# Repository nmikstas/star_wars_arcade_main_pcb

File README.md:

# star_wars_arcade_main_pcb
The source files for the reproduction of the 1983 Star Sars Arcade main PCB. The PCB is designed with Kicad. This project is complete and the PCB is verified working!

# Folder Structure
* BOM - Bill of materials for the main PCB
* Gerbers -The gerber files for the main PCB
* pcb - The Kicad design files for the main PCB

# PCB Specifications
* Layers: 2
* Dimensions: 293mm X 525mm
* Different PCB Design: 1
* PCB Thickness: 1.6mm
* Surface Finish: HASL
* Castellated Holes: No
* Copper Weight: 1oz.

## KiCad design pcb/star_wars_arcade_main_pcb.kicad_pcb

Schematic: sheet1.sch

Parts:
A_6, A_7: LS165A; DIP16
A_8: LS74; DIP14
A_9: LS164A; DIP14
B/C_0: LS138; DIP16
B_1: LS244B; DIP20
B_5: LS86; DIP14
B_6, B_7: LS165A; DIP16
B_8: LS385; DIP20
B_9: LS164A; DIP14
C1, C4, C5, C7, C8, C9, C10, C11, C12, C13, C14, C15, C16, C17, C18, C19, C20, C21, C22, C23, C24, C45, C46, C47, C48, C52, C53, C54, C55, C56, C57, C58, C59, C60, C61, C62, C63, C64, C65, C66, C67, C68, C69, C70, C71, C72, C73, C74, C75, C76, C77, C78, C79, C80, C81, C82, C83, C84, C85, C86, C87, C88, C89, C90, C91, C92, C95, C96: .1uf; GenericComp
C2: 100pf; CapBrown
C3: 39pf; CapBrown
C49, C50, C51: 100uf 35V; LargeCap
C93: 10uf 25V; Cap1
C94: 4.7uf; Cap1
CR1, CR3: 1N914; GenericComp
CR2: BLUE; LED
CR4, CR5, CR6: BLUE LED; LED
C_1: LS244C; DIP20
C_2: 68B09E; DDIP40
C_5: LS164A; DIP14
C_6, C_7: LS384; DIP16
C_8: LS08; DIP14
C_9, C_10: LS161; DIP16
D/E0: LS245A; DIP20
D_3: LS191_; DIP16
D_4, D_6, D_7: LS299; DIP20
D_5: LS164A; DIP14
D_8: LS00; DIP14
D_9: LS161; DIP16
E/F_2: LS244D; DIP20
E_1: x2212; DIP18
E_3: LS191_; DIP16
E_4: LS245A; DIP20
E_5, E_6: LS08; DIP14
E_7: LS00; DIP14
E_8: S02; DIP14
E_9: LS244; DIP20
F/H_2: 137211; DDIP24
F_1: 27128; DIP28
F_3: LS191_; DIP16
F_4: LS245A; DIP20
F_5: RAM; DDIP24
F_6: LS153A; DIP16
F_7: LS00; DIP14
F_8: S10; DIP14
F_9: LS244; DIP20
H/J_1: 2764; DIP28
H_3: LS157A; DIP16
H_4: LS245A; DIP20
H_5: RAM; DDIP24
H_6: LS191_; DIP16
H_7: PROM; DIP18
H_8: LS74; DIP14
H_9: LS244E; DIP20
J16: Aud_Conn; Aud_Con
J17: Main_Connector; J17
J18: Cat_Box_Conn; J21
J20: J20; Edge_Connector
J/K_1: 2764; DIP28
J_2: LS139; DIP16
J_3: LS153A; DIP16
J_4: LS244A; DIP20
J_5: LS164A; DIP14
J_6: LS191_; DIP16
J_7: PROM; DIP18
J_9: LS244F; DIP20
K/L_1: 2764; DIP28
K_2, K_6: LS08; DIP14
K_3: LS153A; DIP16
K_4: LS244A; DIP20
K_5: LS164A; DIP14
K_7: PROM; DIP18
K_8: LS04; DIP14
K_9: ADC; DIP28
L1: 100uH; Ind
L/M_9: LS259; DIP16
L_2, L_8: LS138; DIP16
L_3: LS157B; DIP16
L_4, L_5: LS374; DIP20
L_6: LS175D; DIP16
L_7: PROM; DIP18
L_10: 7407; DIP14
M_1: 2764; DIP28
M_2: LS74; DIP14
M_3: LS00; DIP14
M_4: LS374A; DIP20
M_5: LS374B; DIP20
M_6: LS83A; DIP16
M_7: LS299; DIP20
M_8: LS138; DIP16
N_1: S04; DIP14
N_2: LS161; DIP16
N_3: LS299; DIP20
N_4, N_5, N_6: LS83A; DIP16
N_7: LS138; DIP16
N_8: LS00; DIP14
N_11: 082; DIP8
P_2: LS393; DIP14
P_3: LS04; DIP14
P_4: LS175B; DIP16
P_5: LS175A; DIP16
P_6: LS175C; DIP16
P_7: LS74; DIP14
P_8: LS109; DIP16
Q1: 2N3904; GenericTrans
Q3, Q4: Q_NPN_BCE; VoltReg
R1, R2, R5, R11, R12, R15, R42, R43, R44, R45, R46, R47, R48, R49, R50, R51, R52, R53, R54, R55, R56, R57, R59: 10k; GenericComp
R3: 68; GenericComp
R4, R9, R10, R13, R14, R16, R17, R22, R23, R24, R25, R34, R35, R36, R37, R38, R39, R40, R41, R58, R91, R92, R93, R94, R95, R96, R97: 1k; GenericComp
R6: 100k; GenericComp
R7: 220; GenericComp
R8: 15k; GenericComp
R18, R19, R20, R21, R26, R27, R28, R29, R30, R31, R32, R33: 470; GenericComp
R79, R80, R81: 100; GenericComp
R82, R83, R84, R85, R86: 4.7k; GenericComp
R100: 22k; GenericComp
R1000: 180; GenericComp
R_2: LS393A; DIP14
R_3: LS161; DIP16
R_5: LS155; DIP16
R_6: LS74; DIP14
R_8: LS191_; DIP16
R_10: LS14; DIP14
SPARE1: SpareB; DIP16
SW1: L_11; DIP8
SW2: D_10; DIP16
SW3: E/F_10; DIP16
TP3MHZ1, TP6MHZ1: TP; TEST_POINT
TP+5V1, TP+5V2, TP+5V3, TP+5V4, TP+10.3UN1, TP+12V1: TP; TEST_POINT
TP-5V1: TP; TEST_POINT
TPCATSTR1: TP; TEST_POINT
TPCOINL1: TP; TEST_POINT
TPCOINR1: TP; TEST_POINT
TPCOIN_AUX1: TP; TEST_POINT
TPDIAGN1: TP; TEST_POINT
TPE1: TP; TEST_POINT
TPEVMEM1: TP; TEST_POINT
TPFIRE/START1: TP; TEST_POINT
TPGND1, TPGND2, TPGND3, TPGND4: TP; TEST_POINT
TPHALT1: TP; TEST_POINT
TPMPAGE1: TP; TEST_POINT
TPQ1: TP; TEST_POINT
TPRESET1: TP; TEST_POINT
TPROM0, TPROM1, TPROM2, TPROM3, TPROM4: TP; TEST_POINT
TPRST1, TPRST2: TP; TEST_POINT
TPRW1: TP; TEST_POINT
TPRWB1: TP; TEST_POINT
TPSELF_TEST1: TP; TEST_POINT
TPSLAM1: TP; TEST_POINT
TPWDDIS1: TP; TEST_POINT
VR1: L7805; VoltReg
Y1: 12.096MHz; Y

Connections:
1.5GCLK: D_9.12 (QC), F_7.13
1.5MHZ: B_1.11 (I0b), D_8.5, E_5.9, E_5.10, E_5.12, E_5.13, M_2.2 (1D), M_3.4, N_2.12 (QC), P_3.1
3GCLK: D_9.13 (QB), E_7.1
3MHZ: B_1.6 (I2a), C_5.8 (CLK), D_4.12 (CK~), D_5.8 (CLK), M_2.3 (1CLK), N_2.13 (QB), N_8.2, TP3MHZ1.1, TP3MHZ1.2
3MHZ*: M_3.13, M_4.11 (Cp), M_5.11 (Cp), M_7.3 (G2~), N_3.3 (G2~), P_8.10 (Q), R_6.11 (2CLK)
6MHZ: B_1.8 (I3a), N_2.14 (QA), P_3.11, TP6MHZ1.1, TP6MHZ1.2
12MHZ: C_9.2 (CLK), C_10.2 (CLK), D_9.2 (CLK), E_8.8, E_8.11, N_1.12, N_2.2 (CLK), R1000.1
750KHZ: K_9.10 (CLK), N_2.11 (QD), P_2.13 (2CK), R85.2
+5EAROM: C93.1, C95.2, CR3.1 (K), E_1.18 (VCC), R100.1, VR1.3 (OUT)
+5V: A_6.16 (VCC), A_7.16 (VCC), A_8.14 (VCC), A_9.14 (VCC), B/C_0.16 (VCC), B_1.20 (VCC), B_5.14 (VCC), B_6.16 (VCC), B_7.16 (VCC), B_8.20 (VCC), B_9.14 (VCC), C1.1, C5.1, C21.1, C22.1, C23.1, C24.1, C45.1, C49.1, C52.1, C53.1, C54.1, C55.1, C56.1, C57.1, C58.1, C59.1, C60.1, C61.1, C62.1, C63.1, C64.1, C65.1, C66.1, C67.1, C68.1, C69.1, C70.1, C71.1, C72.1, C73.1, C74.1, C75.1, C76.1, C77.1, C78.1, C79.1, C80.1, C81.1, C82.1, C83.1, C84.1, C85.1, C86.1, C87.1, C88.1, C89.1, C90.1, C91.1, C92.1, C96.1, CR1.1 (K), CR4.2 (A), CR5.2 (A), CR6.2 (A), C_1.20 (VCC), C_2.7 (VCC), C_5.14 (VCC), C_6.16 (VCC), C_7.16 (VCC), C_8.14 (VCC), C_9.16 (VCC), C_10.16 (VCC), D/E0.20 (VCC), D_3.16 (VCC), D_4.20 (VCC), D_5.14 (VCC), D_6.20 (VCC), D_7.20 (VCC), D_8.14 (VCC), D_9.16 (VCC), E/F_2.20 (VCC), E_3.16 (VCC), E_4.20 (VCC), E_5.14 (VCC), E_6.14 (VCC), E_7.14 (VCC), E_8.14 (VCC), E_9.20 (VCC), F/H_2.24 (VCC), F_1.1 (VPP), F_1.27 (PGM), F_1.28 (VCC), F_3.16 (VCC), F_4.20 (VCC), F_5.24 (VCC), F_6.16 (VCC), F_7.14 (VCC), F_8.14 (VCC), F_9.20 (VCC), H/J_1.1 (VPP), H/J_1.26 (NC), H/J_1.27 (PGM), H/J_1.28 (VCC), H_3.16 (VCC), H_4.20 (VCC), H_5.24 (VCC), H_6.16 (VCC), H_7.18 (VCC), H_8.14 (VCC), H_9.20 (VCC), J16.5 (+5V), J17.1 (5V0), J17.2 (5V0), J17.3 (5V0), J17.4 (5V0), J17.83 (5V0), J17.84 (5V0), J17.85 (5V0), J17.86 (5V0), J18.45 (5V0), J18.46 (5V0), J18.47 (5V0), J18.48 (5V0), J18.49 (5V0), J18.50 (5V0), J20.2 (+5V_REG), J20.21 (+SENSE), J20.B (+5V_REG), J20.Y (+5V_REG), J/K_1.1 (VPP), J/K_1.26 (NC), J/K_1.27 (PGM), J/K_1.28 (VCC), J_2.16 (VCC), J_3.16 (VCC), J_4.20 (VCC), J_5.14 (VCC), J_6.16 (VCC), J_7.18 (VCC), J_9.20 (VCC), K/L_1.1 (VPP), K/L_1.26 (NC), K/L_1.27 (PGM), K/L_1.28 (VCC), K_2.14 (VCC), K_3.16 (VCC), K_4.20 (VCC), K_5.14 (VCC), K_6.14 (VCC), K_7.18 (VCC), K_8.14 (VCC), K_9.11 (VCC), K_9.12 (REF+), L/M_9.16 (VCC), L_2.16 (VCC), L_3.16 (VCC), L_4.20 (VCC), L_5.20 (VCC), L_6.16 (VCC), L_7.18 (VCC), L_8.16 (VCC), L_10.14 (VCC), M_1.1 (VPP), M_1.26 (NC), M_1.27 (PGM), M_1.28 (VCC), M_2.14 (VCC), M_3.14 (VCC), M_4.20 (VCC), M_5.20 (VCC), M_6.5 (VCC), M_7.20 (VCC), M_8.16 (VCC), N_1.14 (VCC), N_2.16 (VCC), N_3.20 (VCC), N_4.5 (VCC), N_5.5 (VCC), N_6.5 (VCC), N_7.16 (VCC), N_8.14 (VCC), N_11.2 (-), P_2.14 (VCC), P_3.14 (VCC), P_4.16 (VCC), P_5.16 (VCC), P_6.16 (VCC), P_7.14 (VCC), P_8.16 (VCC), Q1.3 (C), R1.1, R4.1, R10.2, R11.2, R12.2, R15.2, R16.2, R17.2, R18.1, R19.1, R20.1, R21.1, R26.1, R27.1, R28.1, R29.1, R30.1, R31.1, R32.1, R33.1, R42.1, R43.1, R44.1, R45.1, R46.1, R47.1, R48.1, R49.1, R50.1, R51.1, R52.1, R53.1, R54.1, R55.1, R56.1, R57.1, R82.1, R83.1, R84.1, R85.1, R86.1, R91.1, R92.2, R93.2, R94.2, R95.2, R96.2, R97.1, R_2.14 (VCC), R_3.16 (VCC), R_5.16 (VCC), R_6.14 (VCC), R_8.16 (VCC), R_10.14 (VCC), SPARE1.16 (VCC), TP+5V1.1, TP+5V1.2, TP+5V2.1, TP+5V2.2, TP+5V3.1, TP+5V3.2, TP+5V4.1, TP+5V4.2
+10V: C4.1, J20.18 (+10_UNREG), J20.E (+10_UNREG), N_11.8 (VCC), R5.2, TP+10.3UN1.1, TP+10.3UN1.2
+12V: C51.1, J16.7 (+12V), J20.20 (+12VDC), J20.C (+12VDC), TP+12V1.1, TP+12V1.2, VR1.1 (IN)
-5V: C50.2, J16.6 (-5V), J20.19 (-5VDC), J20.D (-5VDC), TP-5V1.1, TP-5V1.2
A0: C_1.17 (I3b), C_2.8 (A0), J18.17 (A0)
A1: C_1.6 (I2a), C_2.9 (A1), J18.18 (A1)
A2: C_1.4 (I1a), C_2.10 (A2), J18.15 (A2)
A3: C_1.2 (I0a), C_2.11 (A3), J18.16 (A3)
A4: C_1.8 (I3a), C_2.12 (A4), J18.13 (A4)
A5: C_1.15 (I2b), C_2.13 (A5), J18.14 (A5)
A6: C_1.13 (I1b), C_2.14 (A6), J18.11 (A6)
A7: C_1.11 (I0b), C_2.15 (A7), J18.12 (A7)
A8: B_1.17 (I3b), C_2.16 (A8), J18.9 (A8)
A9: B_1.15 (I2b), C_2.17 (A9), J18.10 (A9)
A10: B_1.13 (I1b), C_2.18 (A10), J18.7 (A10)
A11: B_1.4 (I1a), C_2.19 (A11), J18.8 (A11)
A12: B_1.2 (I0a), C_2.20 (A12), J18.21 (A12)
A13: C_2.21 (A13), J18.22 (A13), K_2.9
A14: B/C_0.2 (B), C_2.22 (A14), J18.19 (A14)
A15: B/C_0.3 (C), C_2.23 (A15), J18.20 (A15), M_3.9
AB0: C_1.3 (O3b), E_1.6 (A0), F/H_2.8 (AB0), F_1.10 (A0), H/J_1.10 (A0), J17.43 (AB0), J17.44 (AB0), J/K_1.10 (A0), J_2.14 (2A), K/L_1.10 (A0), K_9.25 (ADDA), L/M_9.1 (A), M_1.10 (A0), N_7.1 (A), R83.2, R_5.3 (A1)
AB1: C_1.14 (O2a), E_1.5 (A1), F/H_2.7 (AB1), F_1.9 (A1), H/J_1.9 (A1), J17.35 (AB1), J17.36 (AB1), J/K_1.9 (A1), J_2.13 (2B), K/L_1.9 (A1), K_9.24 (ADDB), L/M_9.2 (B), L_3.14 (4A), M_1.9 (A1), N_7.2 (B), R82.2
AB2: C_1.16 (O1a), E_1.4 (A2), F/H_2.6 (AB2), F_1.8 (A2), H/J_1.8 (A2), J17.33 (AB2), J17.34 (AB2), J/K_1.8 (A2), K/L_1.8 (A2), L/M_9.3 (C), L_3.2 (1A), M_1.8 (A2), N_7.3 (C)
AB3: C_1.18 (O0a), E_1.3 (A3), F/H_2.5 (AB3), F_1.7 (A3), H/J_1.7 (A3), J17.31 (AB3), J17.32 (AB3), J/K_1.7 (A3), J_3.10 (2C0), K/L_1.7 (A3), M_1.7 (A3)
AB4: C_1.12 (O3a), E_1.2 (A4), F/H_2.4 (AB4), F_1.6 (A4), H/J_1.6 (A4), J17.45 (AB4), J17.46 (AB4), J/K_1.6 (A4), K/L_1.6 (A4), K_3.10 (2C0), M_1.6 (A4)
AB5: C_1.5 (O2b), E_1.16 (A5), F/H_2.3 (AB5), F_1.5 (A5), H/J_1.5 (A5), J17.37 (AB5), J17.38 (AB5), J/K_1.5 (A5), J_3.6 (1C0), K/L_1.5 (A5), L_8.1 (A), M_1.5 (A5), M_8.1 (A)
AB6: C_1.7 (O1b), E_1.17 (A6), F/H_2.2 (AB6), F_1.4 (A6), H/J_1.4 (A6), J17.41 (AB6), J17.42 (AB6), J/K_1.4 (A6), K/L_1.4 (A6), K_3.6 (1C0), L_8.2 (B), M_1.4 (A6), M_8.2 (B)
AB7: C_1.9 (O0b), E_1.1 (A7), F/H_2.1 (AB7), F_1.3 (A7), F_6.6 (1C0), H/J_1.3 (A7), J17.39 (AB7), J17.40 (AB7), J/K_1.3 (A7), K/L_1.3 (A7), L_8.3 (C), M_1.3 (A7), M_8.3 (C)
AB8: B_1.3 (O3b), F/H_2.23 (AB8), F_1.25 (A8), H/J_1.25 (A8), H_3.14 (4A), J17.47 (AB8), J17.48 (AB8), J/K_1.25 (A8), K/L_1.25 (A8), L_2.1 (A), M_1.25 (A8)
AB9: B_1.5 (O2b), F/H_2.22 (AB9), F_1.24 (A9), H/J_1.24 (A9), H_3.2 (1A), J17.49 (AB9), J17.50 (AB9), J/K_1.24 (A9), K/L_1.24 (A9), L_2.2 (B), M_1.24 (A9)
AB10: B_1.7 (O1b), F/H_2.19 (AB10), F_1.21 (A10), H/J_1.21 (A10), H_3.5 (2A), J17.51 (AB10), J17.52 (AB10), J/K_1.21 (A10), K/L_1.21 (A10), L_2.3 (C), M_1.21 (A10)
AB11: B_1.16 (O1a), F_1.23 (A11), H/J_1.23 (A11), H_3.11 (3A), J17.53 (AB11), J17.54 (AB11), J/K_1.23 (A11), J_2.2 (1A), K/L_1.23 (A11), M_1.23 (A11)
AB12: B_1.18 (O0a), F_1.2 (A12), H/J_1.2 (A12), J17.59 (AB12), J17.60 (AB12), J/K_1.2 (A12), J_2.3 (1B), K/L_1.2 (A12), M_1.2 (A12)
AB13: B/C_0.1 (A), J17.55 (AB13), J17.56 (AB13), K_2.8
BIC0: E_3.3 (QA), J_3.11 (2C1)
BIC1: E_3.2 (QB), K_3.11 (2C1)
BIC2: E_3.6 (QC), J_3.5 (1C1)
BIC3: E_3.7 (QD), K_3.5 (1C1)
BIC4: F_3.3 (QA), F_6.5 (1C1)
BIC5: F_3.2 (QB), H_3.13 (4B)
BIC6: F_3.6 (QC), H_3.3 (1B)
BIC7: F_3.7 (QD), H_3.6 (2B)
BIC8: D_3.3 (QA), H_3.10 (3B)
CIG*: K_5.2 (B), M_3.12, R_6.9 (2Q)
COIN_AUX: J20.P (COIN_AUX), R32.2, R39.2
COIN_CNTR_1: C7.1, J20.7 (COIN_CNTR_1), Q3.2 (C), SW1.1
COIN_CNTR_2: C8.1, J20.H (COIN_CNTR_2), Q4.2 (C), SW1.8
COIN_L: J20.N (COIN_L), R31.2, R40.2
COIN_R: J20.12 (COIN_R), R30.2, R41.2
D0: C_2.31 (D0), D/E0.11 (B7), E/F_2.18 (O0a), E_1.12 (IO1), E_4.11 (B7), E_9.3 (O3b), F/H_2.9 (D0), F_9.3 (O3b), H_9.7 (O1b), J18.29 (D0), J_9.3 (O3b), K_9.17 (D0)
D1: C_2.30 (D1), D/E0.12 (B6), E/F_2.16 (O1a), E_1.13 (IO2), E_4.12 (B6), E_9.5 (O2b), F/H_2.10 (D1), F_9.5 (O2b), H_9.16 (O1a), J18.30 (D1), J_9.5 (O2b), K_9.14 (D1)
D2: C_2.29 (D2), D/E0.13 (B5), E/F_2.12 (O3a), E_1.14 (IO3), E_4.13 (B5), E_9.7 (O1b), F/H_2.11 (D2), F_9.7 (O1b), H_9.18 (O0a), J18.27 (D2), J_9.7 (O1b), K_9.15 (D2)
D3: C_2.28 (D3), D/E0.14 (B4), E/F_2.3 (O3b), E_1.15 (IO4), E_4.14 (B4), E_9.9 (O0b), F/H_2.13 (D3), F_9.9 (O0b), H_9.3 (O3b), J18.28 (D3), J_9.16 (O1a), K_9.8 (D3)
D4: C_2.27 (D4), D/E0.15 (B3), E/F_2.5 (O2b), E_4.15 (B3), E_9.12 (O3a), F/H_2.14 (D4), F_9.12 (O3a), H_9.9 (O0b), J18.25 (D4), J_9.12 (O3a), K_9.18 (D4)
D5: C_2.26 (D5), D/E0.16 (B2), E/F_2.14 (O2a), E_4.16 (B2), E_9.14 (O2a), F/H_2.15 (D5), F_9.14 (O2a), H_9.12 (O3a), J18.26 (D5), J_9.14 (O2a), K_9.19 (D5)
D6: C_2.25 (D6), D/E0.17 (B1), E/F_2.7 (O1b), E_4.17 (B1), E_9.16 (O1a), F/H_2.16 (D6), F_9.16 (O1a), H_9.14 (O2a), J18.23 (D6), J_9.9 (O0b), K_9.20 (D6)
D7: C_2.24 (D7), D/E0.18 (B0), E/F_2.9 (O0b), E_4.18 (B0), E_9.18 (O0a), F/H_2.17 (D7), F_9.18 (O0a), H_9.5 (O2b), J18.24 (D7), J_9.18 (O0a), K_9.21 (D7), L/M_9.13 (D)
DB0: D_3.15 (A), D_4.16 (H~), E_3.15 (A), E_4.9 (A7), F_4.11 (B7), H_4.11 (B7), H_6.10 (C), J_4.12 (O3a), K_4.12 (O3a), L_4.13 (D4), L_5.18 (D7), L_6.13 (D3), P_4.5 (D1)
DB1: D_4.4 (G~), E_3.1 (B), E_4.8 (A6), F_4.12 (B6), H_4.12 (B6), H_6.9 (D), J_4.14 (O2a), K_4.14 (O2a), L_4.7 (D2), L_5.17 (D6), L_6.12 (D2), P_4.12 (D2)
DB2: D_4.15 (F~), E_3.10 (C), E_4.7 (A5), F_4.13 (B5), H_4.13 (B5), J_4.16 (O1a), J_6.15 (A), K_4.16 (O1a), L_4.14 (D5), L_5.14 (D5), P_4.13 (D3), P_6.13 (D3)
DB3: D_4.5 (E~), E_3.9 (D), E_4.6 (A4), F_4.14 (B4), H_4.14 (B4), J_4.18 (O0a), J_6.1 (B), K_4.18 (O0a), L_4.8 (D3), L_5.13 (D4), L_6.4 (D0), P_4.4 (D0)
DB4: D_4.14 (D~), E_4.5 (A3), F_3.15 (A), F_4.15 (B3), H_4.15 (B3), J_4.3 (O3b), J_6.10 (C), K_4.3 (O3b), L_4.18 (D7), L_5.8 (D3), L_6.5 (D1), P_5.12 (D2)
DB5: D_4.6 (C~), E_4.4 (A2), F_3.1 (B), F_4.16 (B2), H_4.16 (B2), J_4.5 (O2b), J_6.9 (D), K_4.5 (O2b), L_4.17 (D6), L_5.7 (D2), P_5.5 (D1), P_6.5 (D1)
DB6: D_4.13 (B~), E_4.3 (A1), F_3.10 (C), F_4.17 (B1), H_4.17 (B1), J_4.7 (O1b), K_4.7 (O1b), L_4.4 (D1), L_5.4 (D1), P_5.4 (D0), P_6.4 (D0), P_7.12 (2D)
DB7: D_4.7 (A~), E_4.2 (A0), F_3.9 (D), F_4.18 (B0), H_4.18 (B0), H_8.2 (1D), J_4.9 (O0b), K_4.9 (O0b), L_4.3 (D0), L_5.3 (D0), P_5.13 (D3), P_6.12 (D2)
DD0: L_5.19 (O7), M_5.19 (O7), M_6.11 (B1), M_7.16 (H~)
DD1: L_5.16 (O6), M_5.16 (O6), M_6.7 (B2), M_7.4 (G~)
DD2: L_5.15 (O5), M_5.15 (O5), M_6.4 (B3), M_7.15 (F~)
DD3: L_5.12 (O4), M_5.9 (O3), M_6.16 (B4), M_7.5 (E~)
DD4: L_5.9 (O3), M_5.12 (O4), M_7.14 (D~), N_6.11 (B1)
DD5: L_5.6 (O2), M_5.6 (O2), M_7.6 (C~), N_6.7 (B2)
DD6: L_5.5 (O1), M_5.5 (O1), M_7.13 (B~), N_6.4 (B3)
DD7: L_5.2 (O0), M_5.2 (O0), M_7.7 (A~), N_6.16 (B4)
DD8: L_4.12 (O4), M_4.9 (O3), N_3.16 (H~), N_4.11 (B1)
DD9: L_4.6 (O2), M_4.6 (O2), N_3.4 (G~), N_4.7 (B2)
DD10: L_4.15 (O5), M_4.15 (O5), N_3.15 (F~), N_4.4 (B3)
DD11: L_4.9 (O3), M_4.12 (O4), N_3.5 (E~), N_4.16 (B4)
DD12: L_4.19 (O7), M_4.2 (O0), N_3.14 (D~), N_5.11 (B1)
DD13: L_4.16 (O6), M_4.16 (O6), N_3.6 (C~), N_5.7 (B2)
DD14: L_4.5 (O1), M_4.5 (O1), N_3.13 (B~), N_5.4 (B3)
DD15: L_4.2 (O0), M_4.19 (O7), N_3.7 (A~), N_5.16 (B4)
DIAGN: J20.T (DIAGN), R18.2, R25.2
DS0: M_3.3, M_7.1 (S0~), N_3.1 (S0~)
DS1: M_7.19 (S1~), N_3.19 (S1~), N_8.8
E1.5MHZ: B_1.9 (O0b), J17.75 (1.5MHZ), J17.76 (1.5MHZ)
E3MHZ: B_1.14 (O2a), J17.69 (3MHZ), J17.70 (3MHZ)
E6MHZ: B_1.12 (O3a), J17.67 (6MHZ), J17.68 (6MHZ)
E12MHZ: J17.73 (12MHZ), J17.74 (12MHZ), N_1.10
ECLKQ: C_2.35 (Q), J17.77 (ECLKQ), J17.78 (ECLKQ), M_2.6 (~1Q), TPQ1.1, TPQ1.2
GND: A_6.8 (GND), A_6.15 (~CE), A_7.8 (GND), A_7.15 (~CE), A_8.7 (GND), A_9.7 (GND), B/C_0.4 (~G2A), B/C_0.5 (~G2B), B/C_0.8 (GND), B_1.1 (OEa), B_1.10 (GND), B_1.19 (OEb), B_5.7 (GND), B_6.8 (GND), B_6.15 (~CE), B_7.8 (GND), B_7.15 (~CE), B_8.8 (2S/~A), B_8.10 (GND), B_9.7 (GND), C1.2, C3.2, C4.2, C5.2, C7.2, C8.2, C9.2, C10.2, C11.2, C12.2, C13.2, C14.2, C15.2, C16.2, C17.2, C18.2, C19.2, C20.2, C21.2, C22.2, C23.2, C24.2, C45.2, C46.2, C47.2, C48.2, C49.2, C50.1, C51.2, C52.2, C53.2, C54.2, C55.2, C56.2, C57.2, C58.2, C59.2, C60.2, C61.2, C62.2, C63.2, C64.2, C65.2, C66.2, C67.2, C68.2, C69.2, C70.2, C71.2, C72.2, C73.2, C74.2, C75.2, C76.2, C77.2, C78.2, C79.2, C80.2, C81.2, C82.2, C83.2, C84.2, C85.2, C86.2, C87.2, C88.2, C89.2, C90.2, C91.2, C92.2, C93.2, C94.2, C95.1, C96.2, CR2.1 (K), C_1.1 (OEa), C_1.10 (GND), C_1.19 (OEb), C_2.1 (VSS), C_2.39 (TSC), C_5.7 (GND), C_6.8 (GND), C_6.9 (M), C_6.10 (K), C_7.8 (GND), C_8.7 (GND), C_9.4 (B), C_9.6 (D), C_9.8 (GND), C_10.8 (GND), D/E0.10 (GND), D_3.1 (B), D_3.4 (G), D_3.5 (D/U), D_3.8 (GND), D_3.9 (D), D_3.10 (C), D_4.10 (GND), D_4.19 (S1~), D_5.7 (GND), D_6.10 (GND), D_7.10 (GND), D_8.7 (GND), D_9.5 (C), D_9.8 (GND), E/F_2.10 (GND), E_1.8 (VSS), E_3.4 (G), E_3.5 (D/U), E_3.8 (GND), E_4.10 (GND), E_5.7 (GND), E_6.7 (GND), E_7.7 (GND), E_8.5, E_8.7 (GND), E_8.12, E_9.10 (GND), F/H_2.12 (GND), F_1.14 (GND), F_1.22 (~OE), F_3.4 (G), F_3.5 (D/U), F_3.8 (GND), F_4.10 (GND), F_5.12 (GND), F_5.18 (~CE), F_5.20 (~OE), F_6.1 (~1G), F_6.8 (GND), F_6.15 (~2G), F_7.7 (GND), F_8.7 (GND), F_9.10 (GND), H/J_1.14 (GND), H/J_1.22 (~OE), H_3.8 (GND), H_4.10 (GND), H_5.12 (GND), H_5.18 (~CE), H_5.20 (~OE), H_6.1 (B), H_6.4 (G), H_6.5 (D/U), H_6.8 (GND), H_6.15 (A), H_7.8 (~CE1), H_7.9 (GND), H_7.10 (~CE2), H_8.7 (GND), H_8.12 (2D), H_9.10 (GND), J16.4 (AUD_GND), J17.5 (GND), J17.6 (GND), J17.7 (GND), J17.8 (GND), J17.9 (GND), J17.10 (GND), J17.79 (GND), J17.80 (GND), J17.81 (GND), J17.82 (GND), J18.1 (GND), J18.2 (GND), J18.3 (GND), J18.4 (GND), J18.6 (GND), J18.34 (NC), J20.1 (+5V_RTN), J20.3 (GND), J20.4 (GND), J20.13 (GND), J20.22 (-SENSE), J20.A (+5V_RTN), J20.F (GND), J20.R (GND), J20.Z (+5V_RTN), J/K_1.14 (GND), J/K_1.22 (~OE), J_2.8 (GND), J_3.1 (~1G), J_3.8 (GND), J_3.15 (~2G), J_4.10 (GND), J_5.7 (GND), J_6.4 (G), J_6.5 (D/U), J_6.8 (GND), J_7.8 (~CE1), J_7.9 (GND), J_7.10 (~CE2), J_9.10 (GND), K/L_1.14 (GND), K/L_1.22 (~OE), K_2.7 (GND), K_3.1 (~1G), K_3.8 (GND), K_3.15 (~2G), K_4.10 (GND), K_5.7 (GND), K_6.7 (GND), K_7.8 (~CE1), K_7.9 (GND), K_7.10 (~CE2), K_8.7 (GND), K_9.1 (IN3), K_9.2 (IN4), K_9.3 (IN5), K_9.4 (IN6), K_9.5 (IN7), K_9.13 (GND), K_9.16 (GND), K_9.23 (ADDC), L/M_9.8 (GND), L_2.8 (GND), L_3.8 (GND), L_3.15 (E), L_4.10 (GND), L_5.10 (GND), L_6.8 (GND), L_7.8 (~CE1), L_7.9 (GND), L_7.10 (~CE2), L_8.8 (GND), L_10.7 (GND), M_1.14 (GND), M_1.22 (~OE), M_2.7 (GND), M_3.7 (GND), M_4.10 (GND), M_5.10 (GND), M_5.18 (D7), M_6.12 (GND), M_7.10 (GND), M_7.18 (SL), M_8.8 (GND), N_1.7 (GND), N_2.8 (GND), N_3.10 (GND), N_4.12 (GND), N_5.12 (GND), N_6.12 (GND), N_7.8 (GND), N_8.7 (GND), N_11.4 (VSS), P_2.7 (GND), P_3.7 (GND), P_4.8 (GND), P_5.8 (GND), P_6.8 (GND), P_7.2 (1D), P_7.7 (GND), P_8.2 (J), P_8.3 (K), P_8.8 (GND), P_8.13 (K), Q3.3 (E), Q4.3 (E), R2.2, R3.1, R7.1, R8.2, R1000.2, R_2.7 (GND), R_3.3 (A), R_3.4 (B), R_3.6 (D), R_3.8 (GND), R_5.8 (GND), R_6.7 (GND), R_8.1 (B), R_8.5 (D/U), R_8.8 (GND), R_8.9 (D), R_8.10 (C), R_10.7 (GND), SPARE1.8 (GND), SW2.9, SW2.10, SW2.11, SW2.12, SW2.13, SW2.14, SW2.15, SW2.16, SW3.9, SW3.10, SW3.11, SW3.12, SW3.13, SW3.14, SW3.15, SW3.16, TPGND1.1, TPGND1.2, TPGND2.1, TPGND2.2, TPGND3.1, TPGND3.2, TPGND4.1, TPGND4.2, TPRST1.1, TPRST1.2, VR1.2 (GND), Y1.2
IP0: L_3.13 (4B), L_7.14 (D4)
IP1: L_3.3 (1B), L_7.13 (D5)
IP2: J_3.13 (2C3), L_7.12 (D6)
IP3: K_3.13 (2C3), L_7.11 (D7)
IP4: J_3.3 (1C3), K_7.14 (D4)
IP5: K_3.3 (1C3), K_7.13 (D5)
IP6: F_6.3 (1C3), K_7.12 (D6)
IP7: E_6.1, K_7.11 (D7)
IP8: D_6.19 (S1~), D_7.19 (S1~), D_8.9, J_7.14 (D4)
IP9: F_7.12, J_7.13 (D5)
IP10: F_7.1, J_7.12 (D6)
IP11: E_7.5, J_7.11 (D7)
IP12: E_7.13, H_7.14 (D4)
IP13: E_7.10, H_7.13 (D5)
IP14: F_7.5, H_7.12 (D6)
IP15: F_7.9, H_7.11 (D7)
LED1: CR4.1 (K), J20.6 (LED1), R13.1
L_AUDIO: J16.2 (LT_AUD), J20.17 (L_AUDIO)
L_FIRE: J20.10 (L_FIRE), R29.2, R34.2
L_THUMB: J20.S (L_THUMB), R21.2, R22.2
MA0: F_5.8 (A0), H_5.8 (A0), L_3.12 (4Y)
MA1: F_5.7 (A1), H_5.7 (A1), L_3.4 (1Y)
MA2: F_5.6 (A2), H_5.6 (A2), J_3.9 (2Y)
MA3: F_5.5 (A3), H_5.5 (A3), K_3.9 (2Y)
MA4: F_5.4 (A4), H_5.4 (A4), J_3.7 (1Y)
MA5: F_5.3 (A5), H_5.3 (A5), K_3.7 (1Y)
MA6: F_5.2 (A6), F_6.7 (1Y), H_5.2 (A6)
MA7: F_5.1 (A7), H_3.12 (4Y), H_5.1 (A7)
MA8: F_5.23 (A8), H_3.4 (1Y), H_5.23 (A8)
MA9: F_5.22 (A9), H_3.7 (2Y), H_5.22 (A9)
MA10: F_5.19 (A10), H_3.9 (3Y), H_5.19 (A10)
MATH_RUN: F_8.13, H_8.9 (2Q), H_9.15 (I2b)
MDB0: A_7.6 (D7), B_7.6 (D7), C_7.5 (X0), D_7.16 (H~), H_4.9 (A7), H_5.9 (D0)
MDB1: A_7.5 (D6), B_7.5 (D6), C_7.4 (X1), D_7.4 (G~), H_4.8 (A6), H_5.10 (D1)
MDB2: A_7.4 (D5), B_7.4 (D5), C_7.3 (X2), D_7.15 (F~), H_4.7 (A5), H_5.11 (D2)
MDB3: A_7.3 (D4), B_7.3 (D4), C_7.2 (X3), D_7.5 (E~), H_4.6 (A4), H_5.13 (D3)
MDB4: A_7.14 (D3), B_7.14 (D3), C_7.14 (X4), D_7.14 (D~), H_4.5 (A3), H_5.14 (D4)
MDB5: A_7.13 (D2), B_7.13 (D2), C_7.13 (X5), D_7.6 (C~), H_4.4 (A2), H_5.15 (D5)
MDB6: A_7.12 (D1), B_7.12 (D1), C_7.12 (X6), D_7.13 (B~), H_4.3 (A1), H_5.16 (D6)
MDB7: A_7.11 (D0), B_7.11 (D0), C_7.11 (X7), D_7.7 (A~), H_4.2 (A0), H_5.17 (D7)
MDB8: A_6.6 (D7), B_6.6 (D7), C_6.5 (X0), D_6.16 (H~), F_4.9 (A7), F_5.9 (D0)
MDB9: A_6.5 (D6), B_6.5 (D6), C_6.4 (X1), D_6.4 (G~), F_4.8 (A6), F_5.10 (D1)
MDB10: A_6.4 (D5), B_6.4 (D5), C_6.3 (X2), D_6.15 (F~), F_4.7 (A5), F_5.11 (D2)
MDB11: A_6.3 (D4), B_6.3 (D4), C_6.2 (X3), D_6.5 (E~), F_4.6 (A4), F_5.13 (D3)
MDB12: A_6.14 (D3), B_6.14 (D3), C_6.14 (X4), D_6.14 (D~), F_4.5 (A3), F_5.14 (D4)
MDB13: A_6.13 (D2), B_6.13 (D2), C_6.13 (X5), D_6.6 (C~), F_4.4 (A2), F_5.15 (D5)
MDB14: A_6.12 (D1), B_6.12 (D1), C_6.12 (X6), D_6.13 (B~), F_4.3 (A1), F_5.16 (D6)
MDB15: A_6.11 (D0), A_8.2 (1D), A_8.12 (2D), B_6.11 (D0), C_6.11 (X7), D_6.7 (A~), F_4.2 (A0), F_5.17 (D7)
MPA0: H_6.3 (QA), H_7.5 (A0), J_7.5 (A0), K_7.5 (A0), L_7.5 (A0)
MPA1: H_6.2 (QB), H_7.6 (A1), J_7.6 (A1), K_7.6 (A1), L_7.6 (A1)
MPA2: H_6.6 (QC), H_7.7 (A2), J_7.7 (A2), K_7.7 (A2), L_7.7 (A2)
MPA3: H_6.7 (QD), H_7.4 (A3), J_7.4 (A3), K_7.4 (A3), L_7.4 (A3)
MPA4: H_7.3 (A4), J_6.3 (QA), J_7.3 (A4), K_7.3 (A4), L_7.3 (A4)
MPA5: H_7.2 (A5), J_6.2 (QB), J_7.2 (A5), K_7.2 (A5), L_7.2 (A5)
MPA6: H_7.1 (A6), J_6.6 (QC), J_7.1 (A6), K_7.1 (A6), L_7.1 (A6)
MPA7: H_7.17 (A7), J_6.7 (QD), J_7.17 (A7), K_7.17 (A7), L_7.17 (A7)
MPA8: H_7.16 (A8), J_7.16 (A8), K_7.16 (A8), L_7.16 (A8), P_7.9 (2Q)
MPA9: H_7.15 (A9), H_8.5 (1Q), J_7.15 (A9), K_7.15 (A9), L_7.15 (A9)
MPAGE: F_1.26 (MPAGE), L/M_9.9 (Q4), TPMPAGE1.1, TPMPAGE1.2
unnamed: A_6.9 (Q7), A_7.10 (DS)
unnamed: A_6.10 (DS), A_8.9 (2Q)
unnamed: A_7.9 (Q7), B_8.15 (3A)
unnamed: A_8.5 (1Q), B_6.10 (DS)
unnamed: A_9.1 (A), A_9.2 (B), B_9.13 (QH)
unnamed: A_9.13 (QH), B_8.7 (2B)
unnamed: B/C_0.13 (Y2), J_2.1 (1G)
unnamed: B/C_0.14 (Y1), E_6.9
unnamed: B/C_0.15 (Y0), E_6.10
unnamed: B_5.1, C_5.10 (QE)
unnamed: B_5.2, D_5.12 (QG)
unnamed: B_5.3, B_5.4
unnamed: B_5.6, C_5.1 (A), C_5.2 (B)
unnamed: B_6.9 (Q7), B_7.10 (DS)
unnamed: B_7.9 (Q7), B_8.14 (3B)
unnamed: B_8.9 (2S), D_6.11 (SR~)
unnamed: B_8.12 (3S), C_6.15 (Y), C_7.15 (Y)
unnamed: B_9.1 (A), B_9.2 (B), D_7.17 (QH)
unnamed: C2.1, Q1.2 (B), R1.2, R2.1, Y1.1
unnamed: C2.2, C3.1, L1.1, N_1.1, Q1.1 (E)
unnamed: C9.1, H_9.2 (I0a), R25.1, TPDIAGN1.1, TPDIAGN1.2
unnamed: C10.1, H_9.17 (I3b), R24.1
unnamed: C11.1, H_9.11 (I0b), R23.1
unnamed: C12.1, H_9.8 (I3a), R22.1
unnamed: C13.1, J_9.2 (I0a), R34.1, TPFIRE/START1.1, TPFIRE/START1.2
unnamed: C14.1, J_9.11 (I0b), R35.1
unnamed: C15.1, J_9.6 (I2a), R36.1
unnamed: C16.1, J_9.8 (I3a), R37.1, TPSELF_TEST1.1, TPSELF_TEST1.2
unnamed: C17.1, J_9.17 (I3b), R41.1, TPCOINR1.1, TPCOINR1.2
unnamed: C18.1, J_9.15 (I2b), R40.1, TPCOINL1.1, TPCOINL1.2
unnamed: C19.1, J_9.13 (I1b), R39.1, TPCOIN_AUX1.1, TPCOIN_AUX1.2
unnamed: C20.1, J_9.4 (I1a), R38.1, TPSLAM1.1, TPSLAM1.2
unnamed: C46.1, K_9.26 (IN0), R79.1
unnamed: C47.1, K_9.27 (IN1), R80.1
unnamed: C48.1, K_9.28 (IN2), R81.1
unnamed: C94.1, CR3.2 (A), R59.2, R100.2
unnamed: CR1.2 (A), R9.2, R_10.11, TPRST2.1, TPRST2.2
unnamed: CR2.2 (A), R91.2
unnamed: CR5.1 (K), R14.1
unnamed: CR6.1 (K), R58.1
unnamed: C_2.2 (NMI), C_2.4 (FIRQ), R10.1
unnamed: C_2.3 (IRQ), M_2.8 (~2Q)
unnamed: C_2.34 (E), E_5.11, R4.2, TPE1.1, TPE1.2
unnamed: C_5.13 (QH), D_4.11 (SR~)
unnamed: C_6.6 (PROD), C_7.10 (K)
unnamed: C_8.5, C_8.9, C_8.10, D_8.11
unnamed: C_9.12 (QC), C_10.10 (ET), D_8.13, K_8.13
unnamed: C_9.10 (ET), C_10.15 (RCO)
unnamed: D/E0.19 (CE), K_6.8
unnamed: D_3.14 (CK), F_3.13 (RIP)
unnamed: D_4.17 (QH), D_5.1 (A), D_5.2 (B)
unnamed: D_6.17 (QH), D_7.11 (SR~)
unnamed: D_8.1, D_8.2, L/M_9.12 (Q7)
unnamed: D_9.9 (LD), E_8.1
unnamed: D_9.15 (RCO), E_8.3, F_8.9, F_8.10, F_8.11
unnamed: E/F_2.1 (OEa), E/F_2.19 (OEb), K_2.11
unnamed: E/F_2.2 (I0a), F_1.11 (D0), H/J_1.11 (D0), J/K_1.11 (D0), K/L_1.11 (D0), M_1.11 (D0)
unnamed: E/F_2.4 (I1a), F_1.12 (D1), H/J_1.12 (D1), J/K_1.12 (D1), K/L_1.12 (D1), M_1.12 (D1)
unnamed: E/F_2.6 (I2a), F_1.17 (D5), H/J_1.17 (D5), J/K_1.17 (D5), K/L_1.17 (D5), M_1.17 (D5)
unnamed: E/F_2.8 (I3a), F_1.13 (D2), H/J_1.13 (D2), J/K_1.13 (D2), K/L_1.13 (D2), M_1.13 (D2)
unnamed: E/F_2.11 (I0b), F_1.19 (D7), H/J_1.19 (D7), J/K_1.19 (D7), K/L_1.19 (D7), M_1.19 (D7)
unnamed: E/F_2.13 (I1b), F_1.18 (D6), H/J_1.18 (D6), J/K_1.18 (D6), K/L_1.18 (D6), M_1.18 (D6)
unnamed: E/F_2.15 (I2b), F_1.16 (D4), H/J_1.16 (D4), J/K_1.16 (D4), K/L_1.16 (D4), M_1.16 (D4)
unnamed: E/F_2.17 (I3b), F_1.15 (D3), H/J_1.15 (D3), J/K_1.15 (D3), K/L_1.15 (D3), M_1.15 (D3)
unnamed: E_1.10 (~RC), L_10.2, R59.1
unnamed: E_3.13 (RIP), F_3.14 (CK)
unnamed: E_4.19 (CE), K_6.6
unnamed: E_5.2, R_5.11 (Q2b)
unnamed: E_6.5, R_5.9 (Q0b)
unnamed: E_6.11, R_6.2 (1D)
unnamed: E_6.13, R11.1, TPWDDIS1.1, TPWDDIS1.2
unnamed: E_7.2, K_8.8
unnamed: E_8.2, F_8.12
unnamed: E_8.9, F_8.8
unnamed: E_9.2 (I0a), R49.2, SW2.8
unnamed: E_9.4 (I1a), R48.2, SW2.7
unnamed: E_9.6 (I2a), R47.2, SW2.6
unnamed: E_9.8 (I3a), R46.2, SW2.5
unnamed: E_9.11 (I0b), R45.2, SW2.4
unnamed: E_9.13 (I1b), R44.2, SW2.3
unnamed: E_9.15 (I2b), R43.2, SW2.2
unnamed: E_9.17 (I3b), R42.2, SW2.1
unnamed: F_7.11, K_8.9
unnamed: F_9.2 (I0a), R57.2, SW3.8
unnamed: F_9.4 (I1a), R56.2, SW3.7
unnamed: F_9.6 (I2a), R55.2, SW3.6
unnamed: F_9.8 (I3a), R54.2, SW3.5
unnamed: F_9.11 (I0b), R53.2, SW3.4
unnamed: F_9.13 (I1b), R52.2, SW3.3
unnamed: F_9.15 (I2b), R51.2, SW3.2
unnamed: F_9.17 (I3b), R50.2, SW3.1
unnamed: J18.35 (NC), TPCATSTR1.1, TPCATSTR1.2
unnamed: J_2.4 (1Y0), L_2.4 (~G2A), L_2.5 (~G2B)
unnamed: J_2.6 (1Y2), K_2.2
unnamed: J_2.7 (1Y3), K_2.1
unnamed: J_2.15 (2G), N_8.11
unnamed: J_4.2 (I0a), J_5.6 (QD)
unnamed: J_4.4 (I1a), J_5.5 (QC)
unnamed: J_4.6 (I2a), J_5.4 (QB)
unnamed: J_4.8 (I3a), J_5.3 (QA)
unnamed: J_4.11 (I0b), J_5.13 (QH)
unnamed: J_4.13 (I1b), J_5.12 (QG)
unnamed: J_4.15 (I2b), J_5.11 (QF)
unnamed: J_4.17 (I3b), J_5.10 (QE)
unnamed: J_5.2 (B), K_4.11 (I0b), K_5.13 (QH)
unnamed: K_2.5, M_8.14 (Y1)
unnamed: K_2.12, M_3.8
unnamed: K_4.2 (I0a), K_5.6 (QD)
unnamed: K_4.4 (I1a), K_5.5 (QC)
unnamed: K_4.6 (I2a), K_5.4 (QB)
unnamed: K_4.8 (I3a), K_5.3 (QA)
unnamed: K_4.13 (I1b), K_5.12 (QG)
unnamed: K_4.15 (I2b), K_5.11 (QF)
unnamed: K_4.17 (I3b), K_5.10 (QE)
unnamed: K_6.2, M_8.7 (Y7)
unnamed: K_6.12, M_8.10 (Y5)
unnamed: K_8.4, K_9.9 (OE), R86.2
unnamed: K_8.6, K_9.6 (START), K_9.22 (ALE), R84.2
unnamed: K_8.10, N_8.13
unnamed: L1.2, R3.2
unnamed: L/M_9.4 (Q0), L_10.5
unnamed: L/M_9.5 (Q1), L_10.3
unnamed: L/M_9.6 (Q2), R58.2
unnamed: L/M_9.7 (Q3), R14.2
unnamed: L/M_9.11 (Q6), R13.2
unnamed: L_2.11 (Y4), P_3.13
unnamed: L_6.3 (~Q0), M_6.1 (A4)
unnamed: L_6.6 (~Q1), N_6.10 (A1)
unnamed: L_6.11 (~Q2), M_6.8 (A2)
unnamed: L_6.14 (~Q3), M_6.10 (A1)
unnamed: L_10.4, Q3.1 (B), R17.1
unnamed: L_10.6, Q4.1 (B), R16.1
unnamed: M_2.11 (2CLK), P_3.4, R_3.9 (LD)
unnamed: M_3.5, P_3.12
unnamed: M_3.10, R12.1
unnamed: M_3.2, M_3.11
unnamed: M_4.3 (D0), N_4.15 (S4)
unnamed: M_4.4 (D1), N_5.6 (S2)
unnamed: M_4.7 (D2), N_4.9 (S1)
unnamed: M_4.8 (D3), N_6.15 (S4)
unnamed: M_4.13 (D4), N_4.2 (S3)
unnamed: M_4.14 (D5), N_4.6 (S2)
unnamed: M_4.17 (D6), N_5.9 (S1)
unnamed: M_4.18 (D7), N_5.2 (S3)
unnamed: M_5.3 (D0), N_6.2 (S3)
unnamed: M_5.4 (D1), N_6.6 (S2)
unnamed: M_5.7 (D2), N_6.9 (S1)
unnamed: M_5.8 (D3), M_6.2 (S3)
unnamed: M_5.13 (D4), M_6.15 (S4)
unnamed: M_5.14 (D5), M_6.6 (S2)
unnamed: M_5.17 (D6), M_6.9 (S1)
unnamed: M_6.3 (A3), P_6.14 (~Q3)
unnamed: M_6.14 (C4), N_6.13 (C0)
unnamed: M_7.8 (QA), N_3.18 (SL)
unnamed: N_1.2, N_1.11, N_1.13
unnamed: N_4.1 (A4), P_4.3 (~Q0)
unnamed: N_4.3 (A3), P_4.14 (~Q3)
unnamed: N_4.8 (A2), P_4.11 (~Q2)
unnamed: N_4.10 (A1), P_4.6 (~Q1)
unnamed: N_4.13 (C0), N_6.14 (C4)
unnamed: N_4.14 (C4), N_5.13 (C0)
unnamed: N_5.1 (A4), P_5.14 (~Q3)
unnamed: N_5.3 (A3), P_5.3 (~Q0)
unnamed: N_5.8 (A2), P_5.6 (~Q1)
unnamed: N_5.10 (A1), P_5.11 (~Q2)
unnamed: N_5.14 (C4), R_6.12 (2D)
unnamed: N_6.1 (A4), P_6.11 (~Q2)
unnamed: N_6.3 (A3), P_6.3 (~Q0)
unnamed: N_6.8 (A2), P_6.6 (~Q1)
unnamed: N_8.3, R_5.15 (Eb2)
unnamed: N_8.6, R_2.2 (1CLR), R_2.12 (2CLR)
unnamed: N_11.1, R6.1, R7.2, R9.1
unnamed: N_11.3 (+), R5.1, R6.2, R8.1
unnamed: P_2.1 (1CK), P_2.8 (2QD)
unnamed: P_2.6 (1QD), R_2.13 (2CK), R_3.2 (CLK)
unnamed: P_2.2 (1CLR), P_2.12 (2CLR), R_10.9, R_10.10
unnamed: P_3.3, R_3.15 (RCO)
unnamed: P_8.4 (Cp), R_8.13 (RIP)
unnamed: P_8.6 (Q), P_8.14 (J)
unnamed: R_2.1 (1CK), R_2.8 (2QD)
unnamed: R_2.5 (1QC), R_6.3 (1CLK)
P92: B/C_0.6 (G1), B_5.5, C_9.1 (C), C_9.3 (A), C_9.5 (C), C_9.7 (EP), C_10.1 (C), C_10.3 (A), C_10.4 (B), C_10.5 (C), C_10.6 (D), C_10.7 (EP), D_4.1 (S0~), D_4.18 (SL), D_9.1 (C), D_9.3 (A), D_9.4 (B), D_9.6 (D), D_9.7 (EP), D_9.10 (ET), R92.1
P93: A_8.1 (~1CLR), A_8.4 (~1PRE_), A_8.10 (~1PRE_), A_8.13 (~1CLR), B_8.13 (3S/~A), C_7.9 (M), D_6.1 (S0~), D_6.18 (SL), D_7.1 (S0~), D_7.18 (SL), H_8.1 (~1CLR), H_8.4 (~1PRE_), R93.1
P94: F_6.4 (1C2), F_6.10 (2C0), F_6.11 (2C1), F_6.12 (2C2), F_6.13 (2C3), J_5.1 (A), K_2.10, K_5.1 (A), L_2.6 (G1), L_6.1 (C), L_8.6 (G1), M_6.13 (C0), M_7.11 (SR~), M_8.6 (G1), R94.1
P95: N_7.6 (G1), P_5.1 (C), P_6.1 (C), P_7.1 (~1CLR), P_7.10 (~1PRE_), P_7.13 (~1CLR), P_8.1 (Cd), P_8.11 (Sd), R95.1, R_5.1 (Ea1), R_6.1 (~1CLR), R_6.10 (~1PRE_), R_6.13 (~1CLR), R_8.15 (A)
P96: J_3.4 (1C2), J_3.12 (2C2), K_3.4 (1C2), K_3.12 (2C2), M_2.1 (~1CLR), M_2.4 (~1PRE_), M_2.10 (~1PRE_), M_2.12 (2D), N_2.1 (C), N_2.3 (A), N_2.4 (B), N_2.5 (C), N_2.6 (D), N_2.7 (EP), N_2.9 (LD), N_2.10 (ET), N_3.9 (CLR~), N_3.11 (SR~), P_4.1 (C), R96.1, R_3.5 (C), R_3.7 (EP), R_3.10 (ET)
PD0: D/E0.9 (A7), J17.29 (PD0), J17.30 (PD0)
PD1: D/E0.8 (A6), J17.27 (PD1), J17.28 (PD1)
PD2: D/E0.7 (A5), J17.25 (PD2), J17.26 (PD2)
PD3: D/E0.6 (A4), J17.23 (PD3), J17.24 (PD3)
PD4: D/E0.5 (A3), J17.21 (PD4), J17.22 (PD4)
PD5: D/E0.4 (A2), J17.19 (PD5), J17.20 (PD5)
PD6: D/E0.3 (A1), J17.17 (PD6), J17.18 (PD6)
PD7: D/E0.2 (A0), J17.15 (PD7), J17.16 (PD7)
PHASE2: E_5.8, J18.31 (PHASE2)
RC: H_6.13 (RIP), J_6.14 (CK)
R_AUDIO: J16.1 (RT_AUD), J20.U (R_AUDIO)
R_FIRE: J20.14 (R_FIRE), R28.2, R35.2
R_THUMB: J20.15 (R_THUMB), R20.2, R23.2
R~W: C_2.32 (R/~W), J18.32 (R/W), P_3.9, TPRW1.1, TPRW1.2
R~W~B: D/E0.1 (DIR), E_4.1 (DIR), F_4.1 (DIR), H_4.1 (DIR), J17.57 (R/~WB), J17.58 (R/~WB), N_1.4, N_8.12, TPRWB1.1, TPRWB1.2
S1: E_5.6, E_6.2, F_6.14 (A), H_3.1 (S), H_8.13 (~1CLR), J_3.14 (A), K_3.14 (A), L_3.1 (S)
S1_: J16.8 (S1), J20.5 (S1)
S2: E_6.3, F_6.2 (B), H_3.15 (E), J_3.2 (B), K_3.2 (B)
S2_: J16.9 (S2), J20.8 (S2)
SELF_TEST: J20.M (SELF_TEST), R26.2, R37.2
SERIAL_MULT: B_8.6 (2A), C_7.6 (PROD)
SLAM: J20.L (SLAM), R33.2, R38.2
SPARE1: J20.11 (SPARE1), R27.2, R36.2
SPARE2: J20.16 (SPARE2), R19.2, R24.2
VGHALT: H_9.6 (I2a), J17.61 (VGHALT), J17.62 (VGHALT)
WP: D_8.10, E_7.4, E_7.9, E_7.12, E_8.6, E_8.10, F_7.2, F_7.4, F_7.10
~1.5MHZ: P_3.2, R_5.2 (Ea2), R_5.14 (Eb1)
~3MHZ*: J_5.8 (CLK), K_5.8 (CLK), M_4.1 (OE), M_5.1 (OE), N_8.9, P_8.9 (~Q), R_8.14 (CK)
~6MHZ: M_7.12 (CK~), N_3.12 (CK~), P_3.10, P_7.3 (1CLK), P_8.12 (Cp)
~12MHZ: D_8.12, E_8.13
~ADC: K_8.3, L_8.11 (Y4)
~ADCSTART: K_8.5, M_8.9 (Y6)
~AW: E_5.3, H_5.21 (~WE)
~BW: E_6.6, F_5.21 (~WE)
~CLEAR_ACC: C_8.1, D_6.9 (CLR~), D_7.9 (CLR~), E_7.11
~CLR: A_9.9 (C), B_9.9 (C), C_8.3
~DVDDH: L_4.11 (Cp), N_7.9 (Y6)
~DVDDL: L_5.11 (Cp), N_7.7 (Y7)
~DVSRH: J_5.9 (C), K_5.9 (C), L_4.1 (OE), L_5.1 (OE), M_3.1, N_7.11 (Y4), N_8.10, P_4.9 (CK), P_5.9 (CK)
~DVSRL: L_6.9 (CK), N_7.10 (Y5), P_6.9 (CK), P_7.4 (~1PRE_)
~ENA: E_5.4, H_4.19 (CE), R_5.5 (Q2a)
~ENB: E_5.5, F_4.19 (CE), R_5.7 (Q0a)
~EVGGO: J17.71 (~EVGGO), J17.72 (~EVGGO), M_8.15 (Y0)
~EVGRST: J17.63 (~EVGRST), J17.64 (~EVGRST), K_2.6
~EVMEM: E_6.8, J17.65 (~EVMEM), J17.66 (~EVMEM), K_6.9, TPEVMEM1.1, TPEVMEM1.2
~GMCLK: A_6.2 (CP), A_7.2 (CP), A_9.8 (CLK), B_6.2 (CP), B_7.2 (CP), B_8.1 (CLK~), B_9.8 (CLK), C_6.7 (CK), C_7.7 (CK), C_8.8
~HALT: C_2.40 (HALT), J18.5 (~HALT), R15.1, TPHALT1.1, TPHALT1.2
~IN0: J_9.1 (OEa), J_9.19 (OEb), L_8.15 (Y0)
~IN1: H_9.1 (OEa), H_9.19 (OEb), L_8.14 (Y1)
~INCBIC: E_3.14 (CK), E_7.6
~IRQCLR: M_2.13 (~1CLR), M_8.12 (Y3)
~LAC: C_8.2, C_8.4, D_8.8
~LDA: A_6.1 (~PL), A_7.1 (~PL), A_8.11 (2CLK), F_7.8
~LDB: A_8.3 (1CLK), B_6.1 (~PL), B_7.1 (~PL), F_7.6
~LDC: B_8.11 (CLR), C_6.1 (CLR), C_7.1 (CLR), C_9.9 (LD), C_10.9 (LD), E_7.8
~LW: D_6.2 (G1~), D_6.3 (G2~), D_7.2 (G1~), D_7.3 (G2~), E_5.1, E_6.4, E_7.3
~MAC_FLAG: F_8.1, K_8.12
~MBCON: K_6.5, K_8.11, L_2.7 (Y7), N_7.5 (~G2B)
~MBRAM: K_2.3, K_6.4, R_5.13 (A0)
~MHALT: F_7.3, H_8.11 (2CLK)
~MW0: F_8.2, H_6.11 (LD), H_8.3 (1CLK), H_8.10 (~1PRE_), J_6.11 (LD), N_7.15 (Y0), P_7.11 (2CLK)
~MW1: D_3.11 (LD), N_7.14 (Y1)
~MW2: E_3.11 (LD), F_3.11 (LD), N_7.13 (Y2)
~NOVRAM: E_1.7 (~CS), L_2.10 (Y5)
~NSTORE: E_1.9 (~STR), K_6.11
~OLATCH: L/M_9.14 (G), M_8.11 (Y4)
~OPT0: E_9.1 (OEa), E_9.19 (OEb), L_8.13 (Y2)
~OPT1: F_9.1 (OEa), F_9.19 (OEb), L_8.12 (Y3)
~OUTS: L_2.9 (Y6), M_8.4 (~G2A)
~PCLR: K_6.13, N_8.5, R97.2, R_6.4 (~1PRE_), R_10.8
~PITCH: J20.J (~PITCH), R79.2
~PRNG: D_4.2 (G1~), D_4.3 (G2~), J_2.9 (2Y3)
~PRNGCLR: C_5.9 (C), D_4.9 (CLR~), D_5.9 (C), L/M_9.10 (Q5)
~RAM: F/H_2.18 (CE), J_2.5 (1Y1)
~RCLK: C_8.6, D_6.12 (CK~), D_7.12 (CK~)
~RECALL: D_8.3, L_10.1
~REH: J_2.12 (2Y0), J_4.1 (OEa), J_4.19 (OEb)
~REL: J_2.11 (2Y1), K_4.1 (OEa), K_4.19 (OEb)
~REN: M_7.2 (G1~), N_3.2 (G1~), P_8.7 (~Q), R_8.4 (G)
~RESET: C_2.37 (RESET), E_6.12, J20.V (~RESET), K_2.4, K_6.1, L/M_9.15 (C), R_3.1 (C), R_6.6 (~1Q), TPRESET1.1, TPRESET1.2
~ROM0: B/C_0.12 (Y3), F_1.20 (~CE), K_2.13, TPROM0.1, TPROM0.2
~ROM1: B/C_0.11 (Y4), H/J_1.20 (~CE), TPROM1.1, TPROM1.2
~ROM2: B/C_0.10 (Y5), J/K_1.20 (~CE), TPROM2.1, TPROM2.2
~ROM3: B/C_0.9 (Y6), K/L_1.20 (~CE), TPROM3.1, TPROM3.2
~ROM4: B/C_0.7 (Y7), M_1.20 (~CE), TPROM4.1, TPROM4.2
~R~WB: D_8.4, F/H_2.20 (OE), N_1.3, N_8.1, P_3.8
~SOUND: J17.11 (~SOUND), J17.12 (~SOUND), K_6.10, M_3.6
~SOUNDRST: J17.13 (~SOUNDRST), J17.14 (~SOUNDRST), K_6.3
~STP: P_7.6 (~1Q), P_8.5 (Sd), P_8.15 (Cd), R_8.11 (LD)
~SW: L_2.12 (Y3), L_8.4 (~G2A), L_8.5 (~G2B)
~THRUST: J20.9 (~THRUST), R81.2
~WDCLR: M_8.13 (Y2), N_8.4
~WE: D_8.6, E_1.11 (~WE), F/H_2.21 (~WE), M_8.5 (~G2B), N_7.4 (~G2A)
~WP: E_8.4, H_6.14 (CK)
~YAW: J20.K (~YAW), R80.2

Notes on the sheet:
POWER INPUT
CLOCK
DIVIDER CLOCK GENERATOR
QUOTIENT SHIFT REGISTER
DIVIDEND SHIFT REGISTER
DIVIDEND LATCH
DIVIDER CONTROL
DIFFERENCE LATCH
ADDER
DIVISOR INVERTING LATCH
MICROPROCESSOR
POWER-ON RESET
WATCHDOG
INTERRUPT TIMER
ROM
RAM
NON_VOLATILE RAM
ADDRESS DECODERS
MATH ADDRESS DECODERS
TEST AND CONTROL SIGNALS
COIN DOOR OUTPUT
COIN DOOR AND CONTROL PANEL INPUT
OPTION SWITCHES
PSEUDO-RANDOM NUMBER GENERATOR
ANALOG/DIGITAL CONVERTER
MATRIX PROCESSOR ADDRESS SELECTOR
MATRIX PROCESSOR RAM
INSTRUCTION PROM
INSTRUCTION STROBE GATES
ACCUMULATOR
SERIAL SUBTRACTOR
REGISTER A
REGISTER B
SERIAL MULTIPLIER
MULTIPLIER/ACCUMULATOR CLOCK
MATRIX PROCESSOR CLOCK
BLOCK INDEX COUNTER
MATRIX PROCESSOR ADDRESS COUNTER
MATRIX PROCESSOR DATA SELECTOR
ADDRESS AND DATA SELECTOR CONTROL

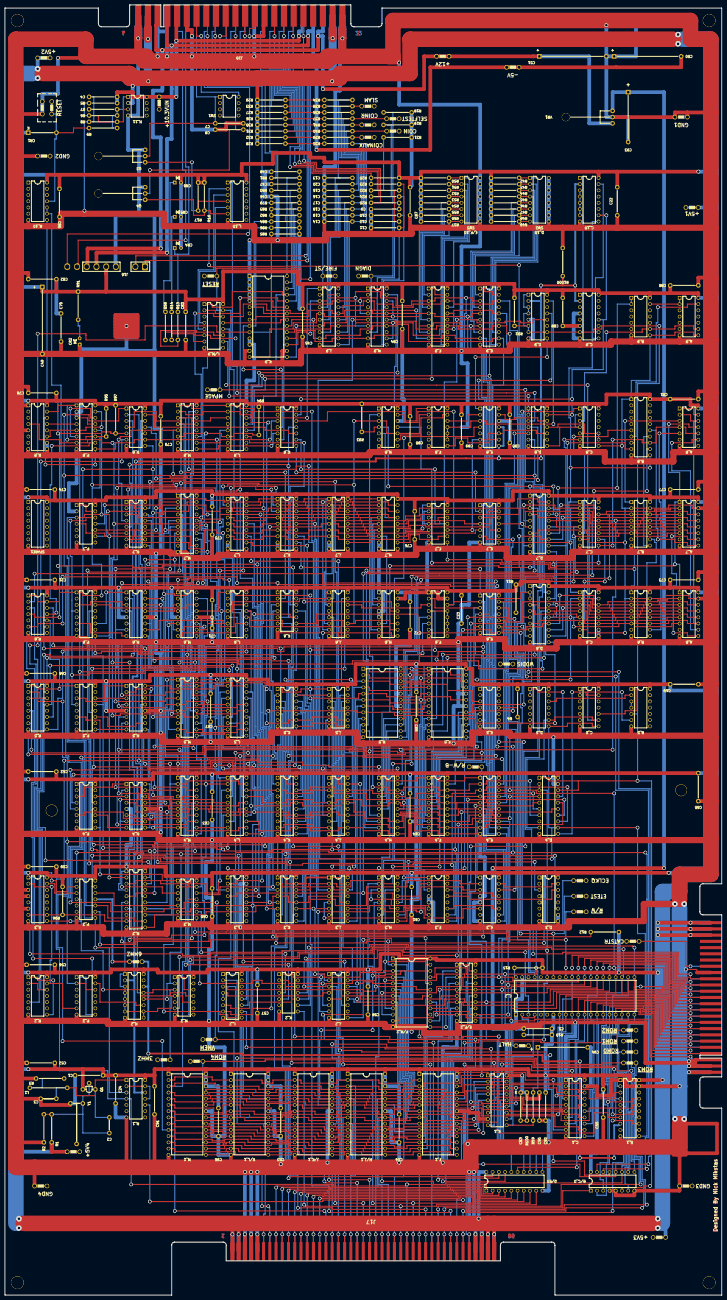
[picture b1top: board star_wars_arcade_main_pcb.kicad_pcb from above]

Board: 2 copper layers, 292.1 x 525.8 mm, 317 parts (0 on the bottom side), 439 nets.

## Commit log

2021-04-28 Started work on the schematic capture
2021-04-28 Continued with the schematic
2021-04-28 Finished microprocessor schematic page
2021-04-29 Added ROM to schematic
2021-04-30 Added RAM to the schematic
2021-05-01 Continued work on the schematic
2021-05-04 Worked on the schematic
2021-05-05 Worked on the mathbox schematic
2021-05-06 Continued the schematic
2021-05-07 Completed the schematic but not error checking
2021-05-07 Fixed most schematic errors
2021-05-23 Fixed all errors on the schematic
2021-05-29 Began the PCB layout
2021-05-31 Placed all the ICs
2021-06-01 Added power traces and components
2021-06-02 Added more power traces and components
2021-06-02 Added more components
2021-06-03 Added more power traces
2021-06-04 Finished the power traces
2021-06-05 Added several components
2021-06-06 Finished placing all components
2021-06-06 Added mounting holes
2021-06-07 Started adding signal traces
2021-06-07 Added more signal traces
2021-06-11 Added more signal traces, 951 disconnected signals remain
2021-06-12 891 unconnected signal remain
2021-06-15 661 unconnected signal remain
2021-06-16 557 unconnected signals remain
2021-06-21 241 unconnected signals remain
2021-06-21 63 disconnected signals remain
2021-06-22 Completed the layout!
2021-06-23 Updated readme file
2021-07-13 Added BOM and fixed minor silkscreen issues
2021-07-13 Updated the BOM
2021-07-18 Fixed some minor silkscreen and BOM issues
2021-07-20 Updated the readme
2022-02-16 Updated BOM, test points on PCB and readme file
